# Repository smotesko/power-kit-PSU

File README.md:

Isolated switch mode power supply for Eurorack synth, ±12V and +5V outputs

See [posts tagged "power-kit"](https://smotesko.com/tags#power-kit) for details.

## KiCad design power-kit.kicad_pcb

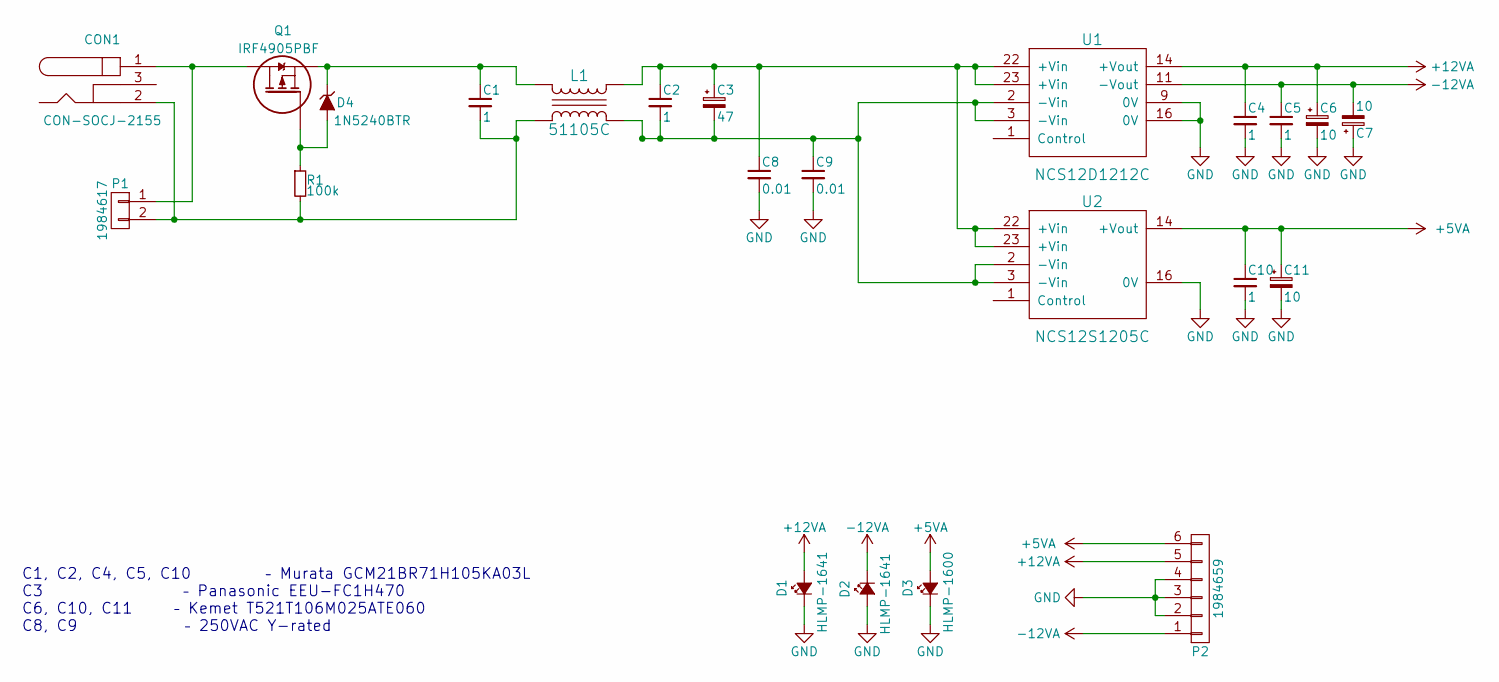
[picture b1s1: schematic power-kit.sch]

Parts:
C1, C2, C4, C5, C10: 1; C_0805_HandSoldering
C3: 47; C_Radial_D6.3_L11.2_P2.5
C6, C7, C11: 10; TantalC_SizeB_EIA-3528_HandSoldering
C8, C9: 0.01; CAP_TH_Radial_15x5_7.5mm
CON1: CON-SOCJ-2155; BARREL_JACK
D1, D2: HLMP-1641; LED-3MM
D3: HLMP-1600; LED-3MM
D4: 1N5240BTR; Diode_DO-35_SOD27_Horizontal_RM10
L1: 51105C; Murata_inductor_5100_series
P1: 1984617; TerminalBlock_Pheonix_PT-3.5mm_2pol
P2: 1984659; TerminalBlock_Pheonix_PT-3.5mm_6pol
Q1: IRF4905PBF; TO-220_Neutral123_Vertical
R1: 100k; Resistor_Horizontal_RM10mm
U1: NCS12D1212C; Murata_NCS12_DC-DC
U2: NCS12S1205C; Murata_NCS12_DC-DC

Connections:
+5VA: C10.1, C11.1, D3.2 (A), P2.6, U2.14 (+Vout)
+12VA: C4.1, C6.1, D1.2 (A), P2.5, U1.14 (+Vout)
-12VA: C5.1, C7.2, D2.1 (K), P2.1, U1.11 (-Vout)
GND: C4.2, C5.2, C6.2, C7.1, C8.2, C9.2, C10.2, C11.2, D1.1 (K), D2.2 (A), D3.1 (K), P2.2, P2.3, P2.4, U1.9 (0V), U1.16 (0V), U2.16 (0V)
unnamed: C1.1, D4.1 (K), L1.4, Q1.3 (S)
unnamed: C1.2, CON1.2, L1.3, P1.2, R1.2
unnamed: C2.1, C3.1, C8.1, L1.1, U1.22 (+Vin), U1.23 (+Vin), U2.22 (+Vin), U2.23 (+Vin)
unnamed: C2.2, C3.2, C9.1, L1.2, U1.2 (-Vin), U1.3 (-Vin), U2.2 (-Vin), U2.3 (-Vin)
unnamed: CON1.1, P1.1, Q1.2 (D)
unnamed: D4.2 (A), Q1.1 (G), R1.1

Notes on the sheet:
C1, C2, C4, C5, C10 – Murata GCM21BR71H105KA03L C3 – Panasonic EEU-FC1H470 C6, C10, C11 – Kemet T521T106M025ATE060 C8, C9 – 250VAC Y-rated

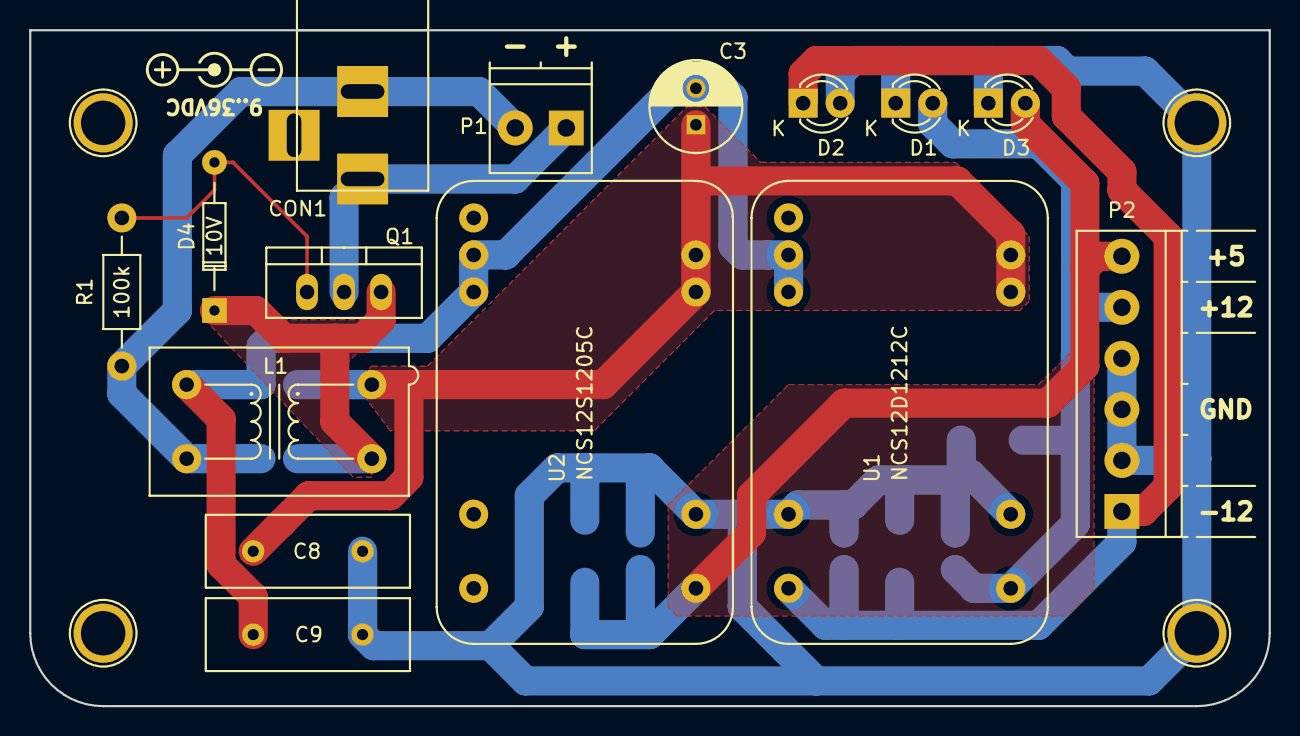
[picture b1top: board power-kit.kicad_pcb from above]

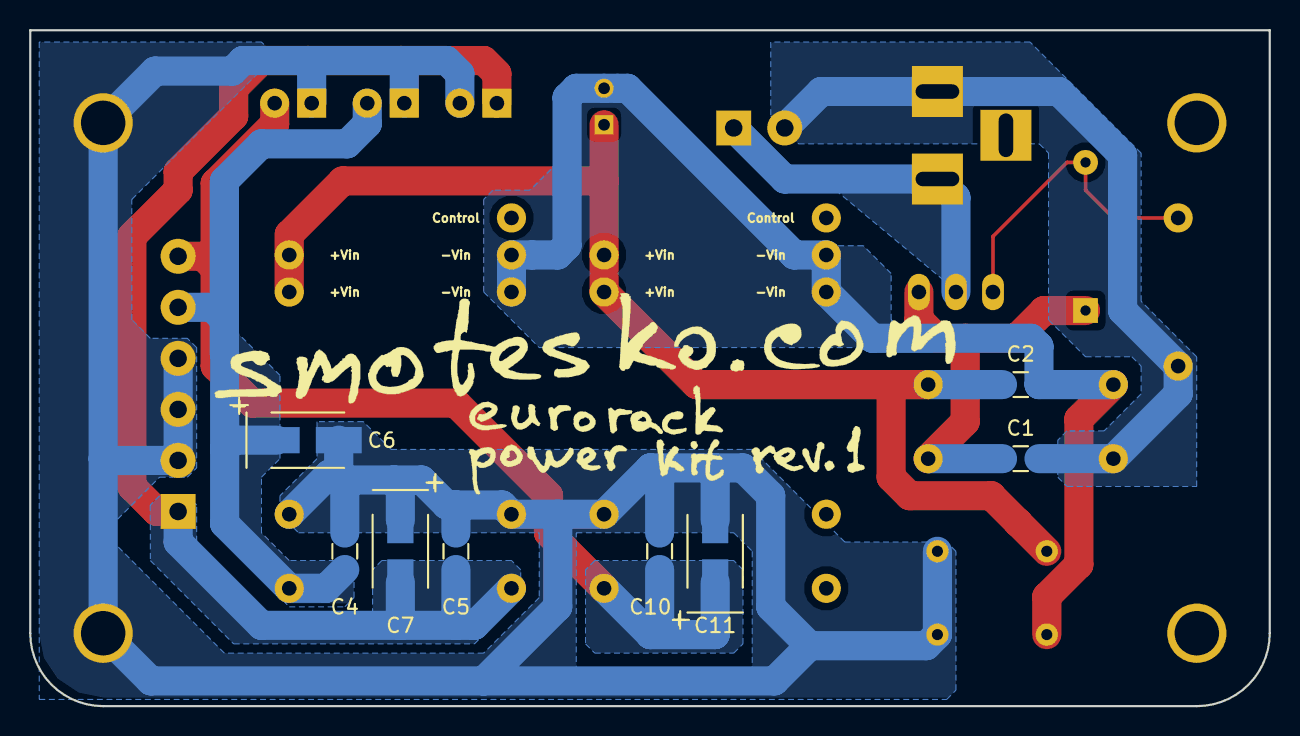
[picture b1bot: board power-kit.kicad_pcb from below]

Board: 2 copper layers, 85.0 x 46.3 mm, 23 parts (8 on the bottom side), 10 nets.

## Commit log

2017-09-03 rev. 1
